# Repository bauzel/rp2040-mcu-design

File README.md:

# RP2040 Minimal Development Board

English 

A minimal RP2040 board with a USB-C connector, designed in KiCad on a 4-layer PCB. This is my first SMD PCB design. I built it by following the "RP2040 Minimal Circuit Design" guide on [schemalyzer.com](https://www.schemalyzer.com/en/blog/microcontrollers/rp2040/minimal-circuit-design).

## Status

> **The board has not been manufactured or tested yet.**

The design currently passes KiCad's **ERC** (schematic) and **DRC** (PCB) checks only. Nothing has been verified on real hardware, so please run your own checks before ordering this design.

### Known DRC exceptions

A few DRC items are excluded on purpose:

- **USB-C connector (4 items):** The distance between the connector's two locating holes (NPTH) and the neighboring GND pads is 0.1944 mm, while my rule is 0.25 mm. This value comes from the connector footprint's own geometry. It is close to the NPTH clearance a PCB fab states, so it should be checked in the fab's DFM review before ordering.
- **Board edge (1 item):** A pad on the front copper layer (F.Cu) is 0.4 mm from the board edge, while my rule is 0.5 mm. This is above the fab's minimum for outer layers.

## Features

- **MCU:** RP2040 (QFN-56)
- **Flash:** Winbond W25Q32JVSS (4 MB, QSPI)
- **Clock:** 12 MHz crystal with two 33 pF load capacitors
- **Power:** USB-C VBUS (5 V) feeding an XC6206-series 3.3 V LDO. The LDO has a low current limit, so check its datasheet if you plan to power external loads.
- **USB:** USB-C connector, 27 Ω series resistors on D+/D−, separate 5.1 kΩ resistors on CC1 and CC2
- **Buttons:** BOOTSEL and RESET
- **Debug:** 3-pin SWD header
- **PCB:** 4 layers (F.Cu / In1.Cu GND plane / In2.Cu +3.3 V plane / B.Cu), 0603 passives

## Programming

Hold the BOOTSEL button while plugging the board into USB (or hold it while pressing RESET). The board appears as a USB mass-storage device, and you can drag and drop a `.uf2` file onto it. This flow has not been tried on a real board yet.

## Broken-out pins

Only **11 of the RP2040's 30 GPIOs** are routed to the headers. The remaining GPIOs are not connected and are left open for anyone who wants to extend the design (the corresponding header pins are unused).

Header pin numbers are the pad numbers on the PCB (pin 1 has a square pad).

**Top header**

| Header pin | GPIO |
|---|---|
| 9 | GPIO6 |
| 10 | GPIO5 |
| 11 | GPIO4 |
| 12 | GPIO3 |
| 13 | GPIO2 |
| 14 | GPIO1 |
| 15 | GPIO0 |

**Bottom header**

| Header pin | GPIO |
|---|---|
| 12 | GPIO20 |
| 13 | GPIO21 |
| 14 | GPIO25 |
| 15 | GPIO22 |

### SWD (debug) header

| Pin | Signal |
|---|---|
| 1 | SWCLK |
| 2 | GND |
| 3 | SWD (SWDIO) |

The pin order was chosen to match the Raspberry Pi Debug Probe cable. Please verify this against the probe's documentation before connecting it.

## Notes and verification against the datasheet

I compared the design with the RP2040 datasheet and Raspberry Pi's "Hardware design with RP2040" document:

- **Power and decoupling:** 100 nF on each IOVDD (6) and DVDD (2) pin, on USB_VDD and on ADC_AVDD, 1 µF on VREG_VIN and VREG_VOUT, TESTEN tied to GND and 27 Ω series resistors on USB_DP/USB_DM all follow the datasheet's requirements.
- **QSPI pin numbers:** This project uses the numbers from the datasheet pin table (QSPI_SD3 = 51, SCLK = 52, SD0 = 53, SD2 = 54, SD1 = 55, SS = 56, GND pad = 57). Most QSPI pin numbers in the guide's flash table do not match the datasheet (it lists QSPI_SS as pin 57, for example), and some pin ranges in its GPIO table are off as well.
- **Crystal circuit (deviation from the reference):** Raspberry Pi's reference design uses the Abracon ABM8-272-T3 (12 MHz, CL = 10 pF, ESR up to 50 Ω), two 15 pF load capacitors and a 1 kΩ series resistor on XOUT, and states that any deviation needs extensive testing. This board follows the guide instead: a 20 pF crystal with 2 × 33 pF load capacitors and no series resistor. The load capacitance math is consistent (33 pF / 2 + 3 pF stray ≈ 19.5 pF), but this is not the reference circuit and has not been tested.
- **Load capacitor values:** The guide's text and BOM disagreed (33 pF vs. 27 pF). This project uses 33 pF for a 20 pF crystal.
- **QSPI_SS pull-up:** There is no external pull-up on QSPI_SS. Raspberry Pi's reference design leaves it unpopulated for the W25Q flash, but it may matter if you use a different flash.

## Possible improvements

- Break out the remaining GPIOs to the headers
- ESD protection on the USB lines and protection on VBUS
- Test points and mounting holes
- Match Raspberry Pi's reference crystal circuit (ABM8-272-T3, 2 × 15 pF, 1 kΩ series resistor on XOUT), or characterize the current one over temperature
- A 3.3 V regulator with a higher current rating
- A BOM and production files (Gerber, pick-and-place)

## Tools

- KiCad (schematic and PCB)

## License

This work is dedicated to the public domain under [CC0 1.0 Universal](https://creativecommons.org/publicdomain/zero/1.0/). You can copy, modify and use it for any purpose, including commercially, without asking for permission. See the `LICENSE` file.

This design is provided **as is, without warranty of any kind**. The author takes no responsibility for any damage or loss resulting from its use. Build and use it at your own risk.

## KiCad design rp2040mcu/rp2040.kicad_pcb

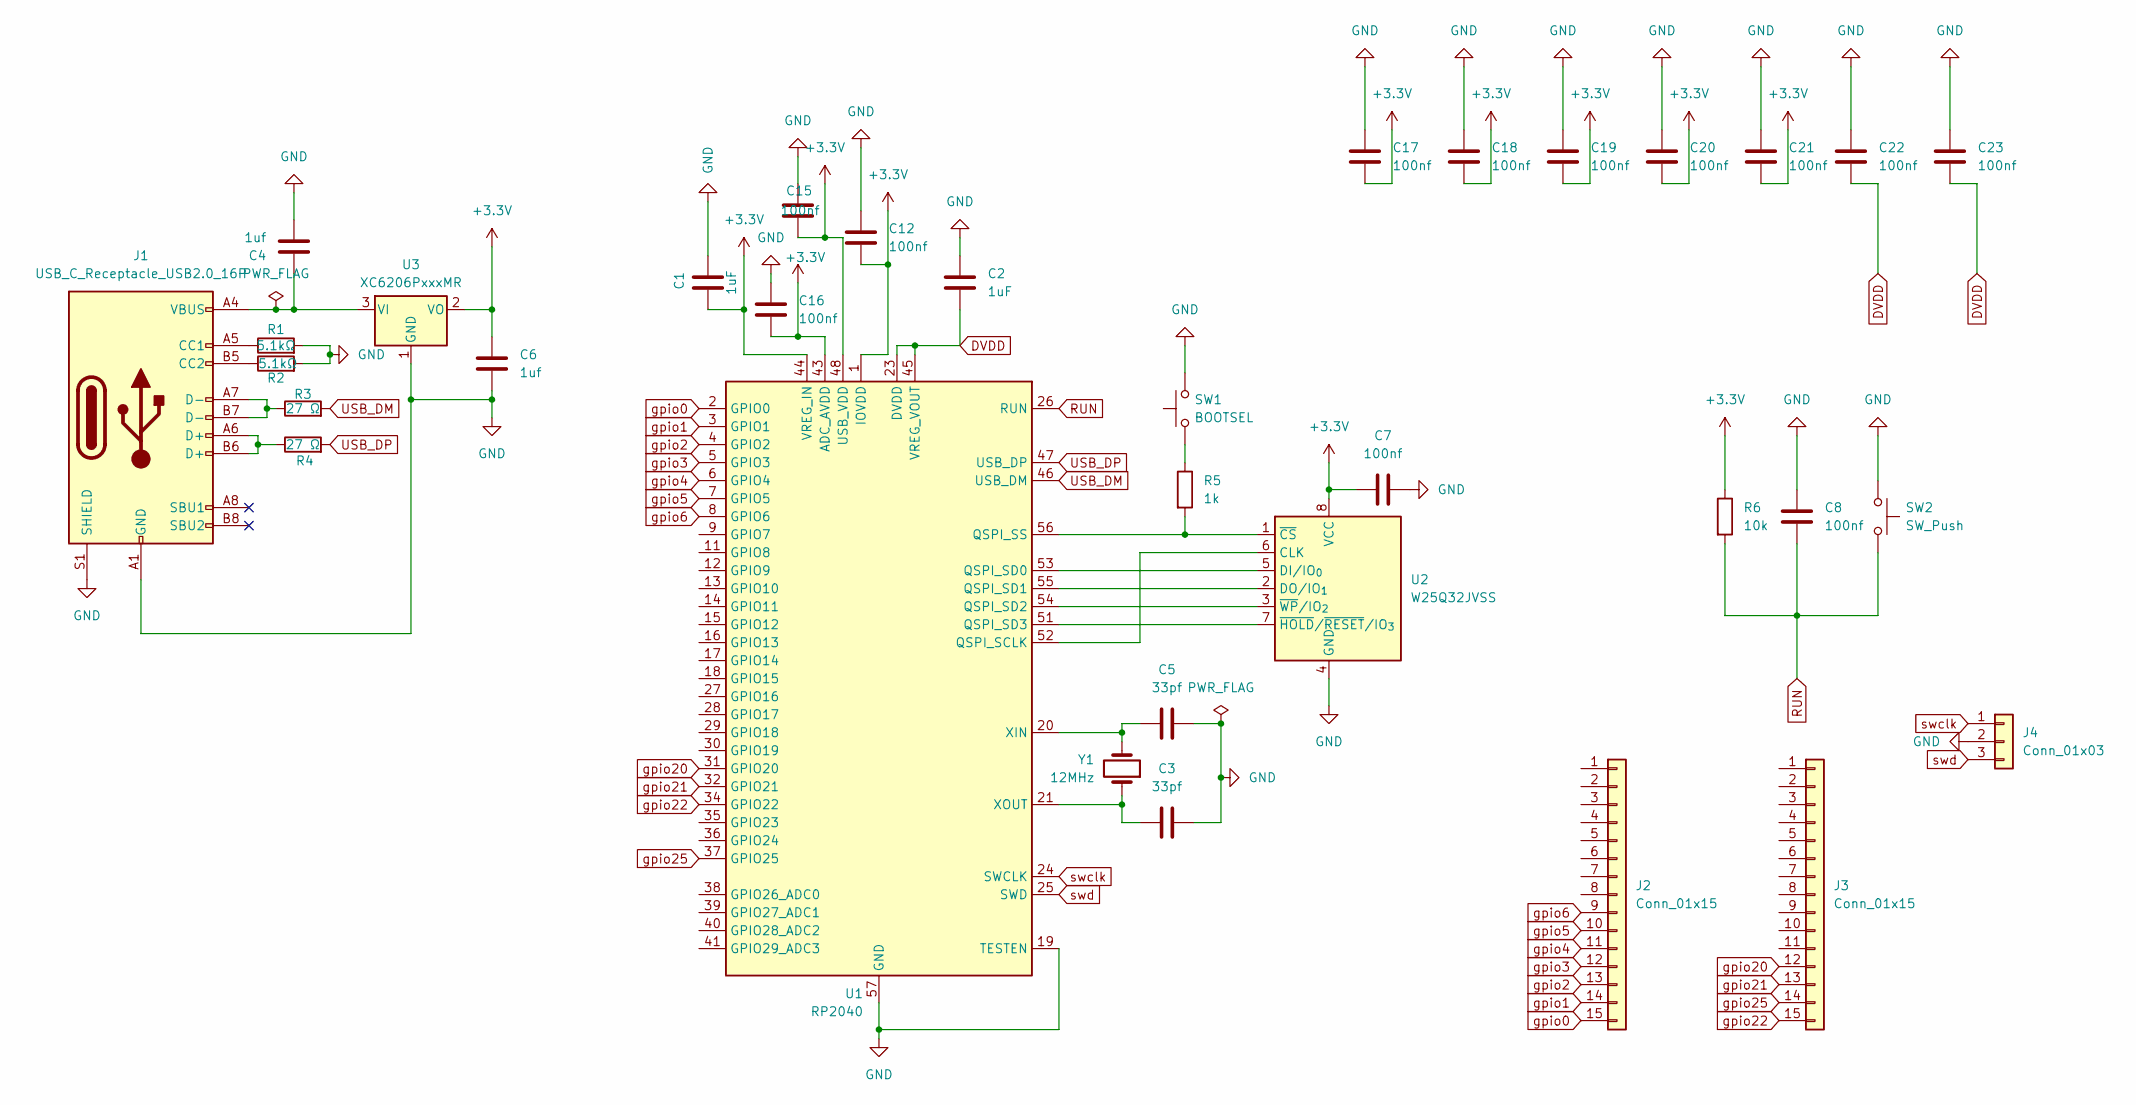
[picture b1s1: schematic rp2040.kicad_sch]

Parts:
C1, C2: 1uF; C_0603_1608Metric
C3, C5: 33pf; C_0603_1608Metric
C4, C6: 1uf; C_0603_1608Metric
C7, C8, C12, C15, C16, C17, C18, C19, C20, C21, C22, C23: 100nf; C_0603_1608Metric
J1: USB_C_Receptacle_USB2.0_16P; USB_C_Receptacle_GCT_USB4105-xx-A_16P_TopMnt_Horizontal
J2, J3: Conn_01x15; PinHeader_1x15_P2.54mm_Vertical
J4: Conn_01x03; PinHeader_1x03_P2.54mm_Vertical
R1, R2: 5.1kΩ; R_0603_1608Metric
R3, R4: 27 Ω; R_0603_1608Metric
R5: 1k; R_0603_1608Metric
R6: 10k; R_0603_1608Metric
SW1: BOOTSEL; SW_SPST_B3U-1000P
SW2: SW_Push; SW_SPST_B3U-1000P
U1: RP2040; QFN-56-1EP_7x7mm_P0.4mm_EP3.2x3.2mm
U2: W25Q32JVSS; SOIC-8_5.3x5.3mm_P1.27mm
U3: XC6206PxxxMR; SOT-23-3
Y1: 12MHz; Crystal_SMD_5032-2Pin_5.0x3.2mm

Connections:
+3.3V: C1.1, C6.1, C7.1, C12.2, C15.2, C16.2, C17.2, C18.2, C19.2, C20.2, C21.2, R6.1, U1.1 (IOVDD), U1.10 (IOVDD), U1.22 (IOVDD), U1.33 (IOVDD), U1.42 (IOVDD), U1.43 (ADC_AVDD), U1.44 (VREG_IN), U1.48 (USB_VDD), U1.49 (IOVDD), U2.8 (VCC), U3.2 (VO)
DVDD: C2.2, C22.2, C23.2, U1.23 (DVDD), U1.45 (VREG_VOUT), U1.50 (DVDD)
GND: C1.2, C2.1, C3.2, C4.2, C5.2, C6.2, C7.2, C8.1, C12.1, C15.1, C16.1, C17.1, C18.1, C19.1, C20.1, C21.1, C22.1, C23.1, J1.A1 (GND), J1.A12 (GND), J1.B1 (GND), J1.B12 (GND), J1.S1 (SHIELD), J4.2, R1.2, R2.2, SW1.2, SW2.1, U1.19 (TESTEN), U1.57 (GND), U2.4 (GND), U3.1 (GND)
unnamed: J1.A5 (CC1), R1.1
unnamed: J1.B5 (CC2), R2.1
unnamed: J1.A6 (D+), J1.B6 (D+), R4.1
unnamed: J1.A7 (D-), J1.B7 (D-), R3.1
unnamed: R5.1, SW1.1
unnamed: U1.52 (QSPI_SCLK), U2.6 (CLK)
unnamed: U1.53 (QSPI_SD0), U2.5 (DI/IO_{0})
unnamed: U1.55 (QSPI_SD1), U2.2 (DO/IO_{1})
unnamed: U1.54 (QSPI_SD2), U2.3 (~WP/IO_{2})
unnamed: U1.51 (QSPI_SD3), U2.7 (~HOLD/~RESET/IO_{3})
unnamed: R5.2, U1.56 (QSPI_SS), U2.1 (~CS)
unnamed: C5.1, U1.20 (XIN), Y1.2
unnamed: C3.1, U1.21 (XOUT), Y1.1
unnamed: C4.1, J1.A4 (VBUS), J1.A9 (VBUS), J1.B4 (VBUS), J1.B9 (VBUS), U3.3 (VI)
RUN: C8.2, R6.2, SW2.2, U1.26 (RUN)
USB_DM: R3.2, U1.46 (USB_DM)
USB_DP: R4.2, U1.47 (USB_DP)
gpio0: J2.15, U1.2 (GPIO0)
gpio1: J2.14, U1.3 (GPIO1)
gpio2: J2.13, U1.4 (GPIO2)
gpio3: J2.12, U1.5 (GPIO3)
gpio4: J2.11, U1.6 (GPIO4)
gpio5: J2.10, U1.7 (GPIO5)
gpio6: J2.9, U1.8 (GPIO6)
gpio20: J3.12, U1.31 (GPIO20)
gpio21: J3.13, U1.32 (GPIO21)
gpio22: J3.15, U1.34 (GPIO22)
gpio25: J3.14, U1.37 (GPIO25)
swclk: J4.1, U1.24 (SWCLK)
swd: J4.3, U1.25 (SWD)

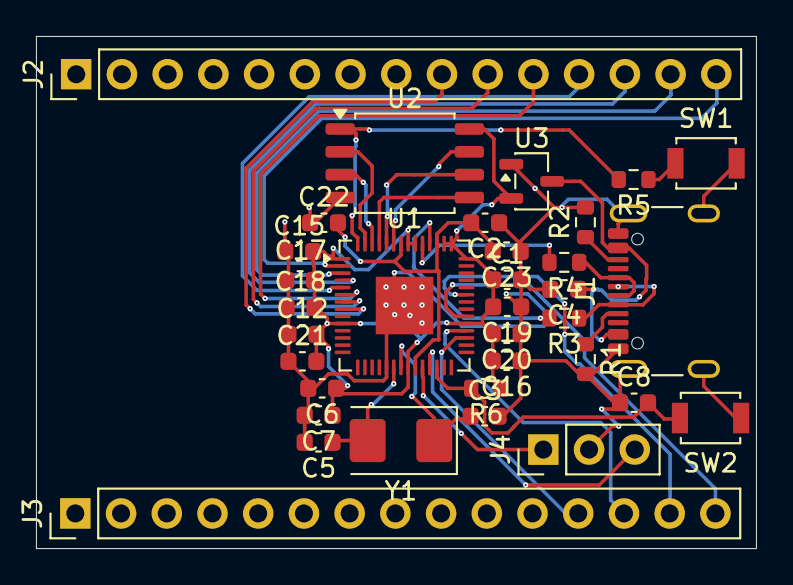
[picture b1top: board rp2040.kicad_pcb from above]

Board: 4 copper layers, 40.0 x 28.4 mm, 34 parts (0 on the bottom side), 33 nets.
